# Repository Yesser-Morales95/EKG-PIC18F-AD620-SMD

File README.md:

# EKG-PIC18F-AD620-SMD
C, Labview.

Esquematico Eagle cadsoft .BRD .SCH

Design 

Board

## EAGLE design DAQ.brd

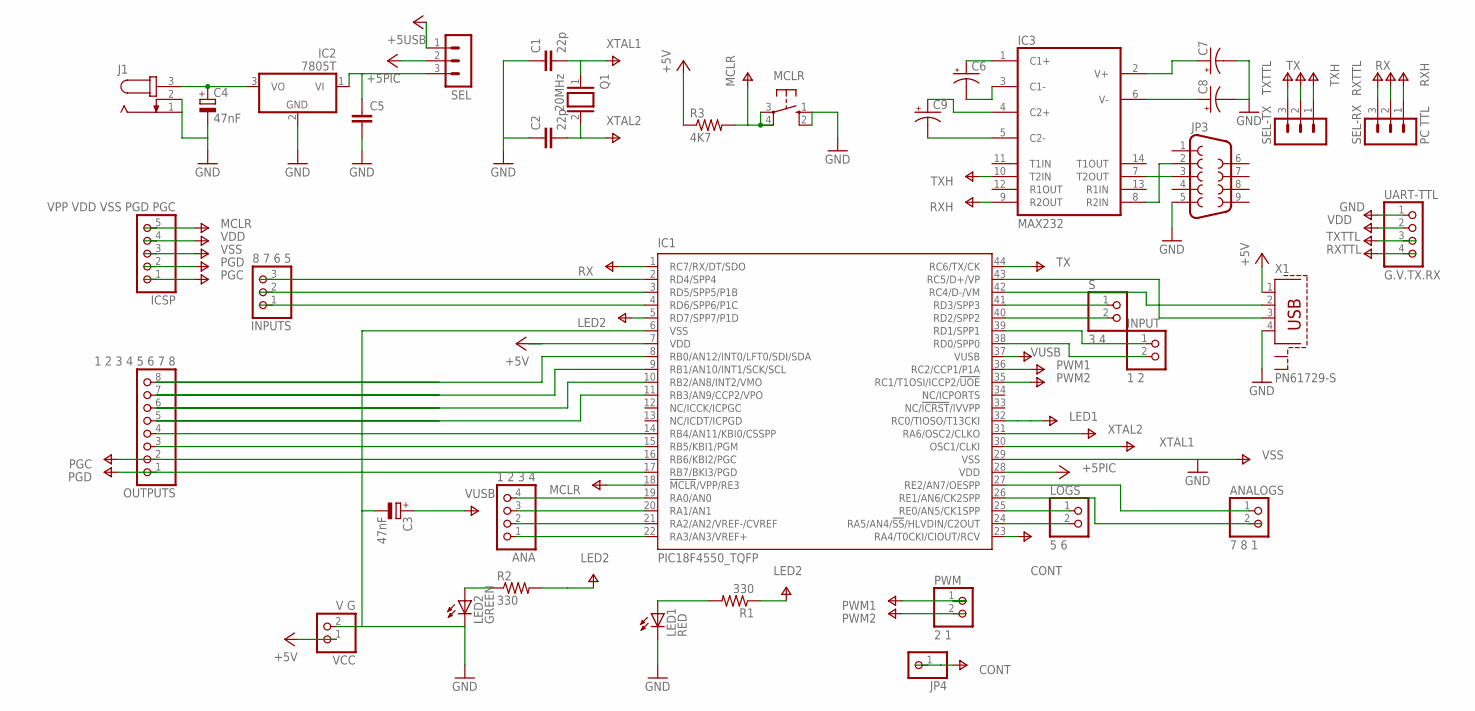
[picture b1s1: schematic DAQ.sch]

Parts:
ANA: 1 2 3 4; 1X04
ANALOGS: 7 8 1; 1X02
C1, C2: 22p; C025-024X044
C3, C4: 47nF; E2,5-6E
C5: C-EU050-035X075; C050-035X075
C6, C7, C8, C9: CPOL-USE2.5-6; E2,5-6
IC1: PIC18F4550_TQFP; TQFP44
IC2: 7805T; TO220H
IC3: MAX232; DIL16
ICSP: VPP VDD VSS PGD PGC; 1X05
INPUT: 1 2; 1X02
INPUTS: 8 7 6 5; 1X03
J1: JACK-PLUG0; SPC4077
JP3: DB9MALE; DB9_MALE
JP4: PINHD-1X1; 1X01
LED1: RED; LED3MM
LED2: GREEN; LED3MM
LOGS: 5 6; 1X02
MCLR: 10-XX; B3F-10XX
OUTPUTS: 1 2 3 4 5 6 7 8; 1X08
PWM: 2 1; 1X02
Q1: 20MHz; QS
R1, R2: 330; 0207/10
R3: 4K7; 0207/10
S: 3 4; 1X02
SEL: MA03-1
SEL-RX: PC TTL; MA03-1
SEL-TX: MA03-1
UART-TTL: G.V.TX.RX; 1X04
VCC: V G; 1X02
X1: PN61729-S

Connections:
+5PIC: IC1.7 (VDD), IC1.28 (VDD), IC3.16 (VCC), ICSP.4, R3.1, SEL.2, UART-TTL.2, VCC.1
+5USB: SEL.1, X1.1
CONT: IC1.23 (RA4/T0CKI/CIOUT/RCV), JP4.1
GND: C1.1, C2.1, C3.-, C4.-, C5.2, C7.-, C8.-, IC1.6 (VSS), IC1.29 (VSS), IC2.2 (GND), IC3.15 (GND), ICSP.3, J1.1, J1.2, JP3.5, LED1.K (C), LED2.K (C), MCLR.1 (S), MCLR.2 (S1), UART-TTL.1, VCC.2, X1.4
LED1: IC1.32 (RC0/TIOSO/T13CKI), R2.2
LED2: IC1.5 (RD7/SPP7/P1D), R1.1
MCLR: IC1.18 (!MCLR!/VPP/RE3), ICSP.5, MCLR.3, MCLR.4 (P1), R3.2
unnamed: IC1.42 (RC4/D-/VM), X1.2
unnamed: C7.+, IC3.2 (V+)
unnamed: C8.+, IC3.6 (V-)
unnamed: IC1.8 (RB0/AN12/INT0/LFT0/SDI/SDA), OUTPUTS.8
unnamed: LED2.A, R2.1
unnamed: C6.+, IC3.1 (C1+)
unnamed: LED1.A, R1.2
unnamed: C6.-, IC3.3 (C1-)
unnamed: IC1.15 (RB5/KBI1/PGM), OUTPUTS.3
unnamed: IC1.14 (RB4/AN11/KBI0/CSSPP), OUTPUTS.4
unnamed: IC1.11 (RB3/AN9/CCP2/VPO), OUTPUTS.5
unnamed: IC1.9 (RB1/AN10/INT1/SCK/SCL), OUTPUTS.7
unnamed: IC1.10 (RB2/AN8/INT2/VMO), OUTPUTS.6
unnamed: C9.+, IC3.4 (C2+)
unnamed: IC1.43 (RC5/D+/VP), X1.3
unnamed: IC1.2 (RD4/SPP4), INPUTS.3
unnamed: IC1.3 (RD5/SPP5/P1B), INPUTS.2
unnamed: IC1.4 (RD6/SPP6/P1C), INPUTS.1
unnamed: IC1.38 (RD0/SPP0), INPUT.2
unnamed: C9.-, IC3.5 (C2-)
unnamed: IC1.40 (RD2/SPP2), S.2
unnamed: IC1.41 (RD3/SPP3), S.1
unnamed: ANA.4, IC1.19 (RA0/AN0)
unnamed: ANA.3, IC1.20 (RA1/AN1)
unnamed: ANA.2, IC1.21 (RA2/AN2/VREF-/CVREF)
unnamed: ANA.1, IC1.22 (RA3/AN3/VREF+)
unnamed: IC1.24 (RA5/AN4/!SS!/HLVDIN/C2OUT), LOGS.2
unnamed: IC1.25 (RE0/AN5/CK1SPP), LOGS.1
unnamed: IC1.39 (RD1/SPP1), INPUT.1
unnamed: ANALOGS.2, IC1.26 (RE1/AN6/CK2SPP)
unnamed: ANALOGS.1, IC1.27 (RE2/AN7/OESPP)
unnamed: IC3.7 (T2OUT), JP3.3
unnamed: IC3.8 (R2IN), JP3.2
unnamed: C4.+, IC2.3 (VO), J1.3
unnamed: C5.1, IC2.1 (VI), SEL.3
PGC: IC1.16 (RB6/KBI2/PGC), ICSP.1, OUTPUTS.2
PGD: IC1.17 (RB7/BKI3/PGD), ICSP.2, OUTPUTS.1
PWM1: IC1.36 (RC2/CCP1/P1A), PWM.1
PWM2: IC1.35 (RC1/T1OSI/ICCP2/!UOE), PWM.2
RX: IC1.1 (RC7/RX/DT/SDO), SEL-RX.2
RXH: IC3.9 (R2OUT), SEL-RX.1
RXTTL: SEL-RX.3, UART-TTL.4
TX: IC1.44 (RC6/TX/CK), SEL-TX.2
TXH: IC3.10 (T2IN), SEL-TX.1
TXTTL: SEL-TX.3, UART-TTL.3
VUSB: C3.+, IC1.37 (VUSB)
XTAL1: C1.2, IC1.30 (OSC1/CLKI), Q1.1
XTAL2: C2.2, IC1.31 (RA6/OSC2/CLKO), Q1.2

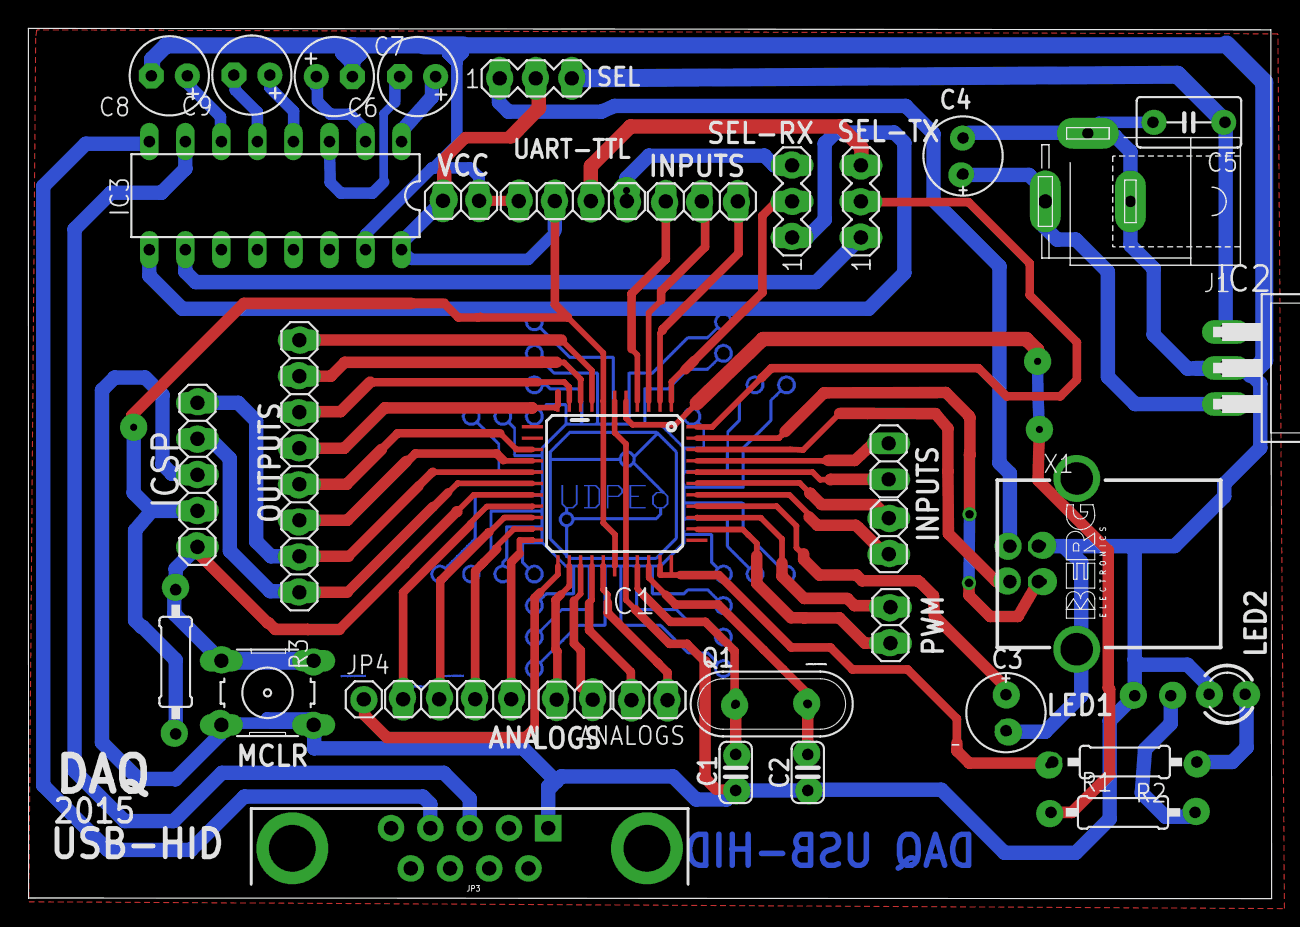
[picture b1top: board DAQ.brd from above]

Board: 2 copper layers, 87.6 x 61.4 mm, 37 parts (1 on the bottom side), 55 nets.

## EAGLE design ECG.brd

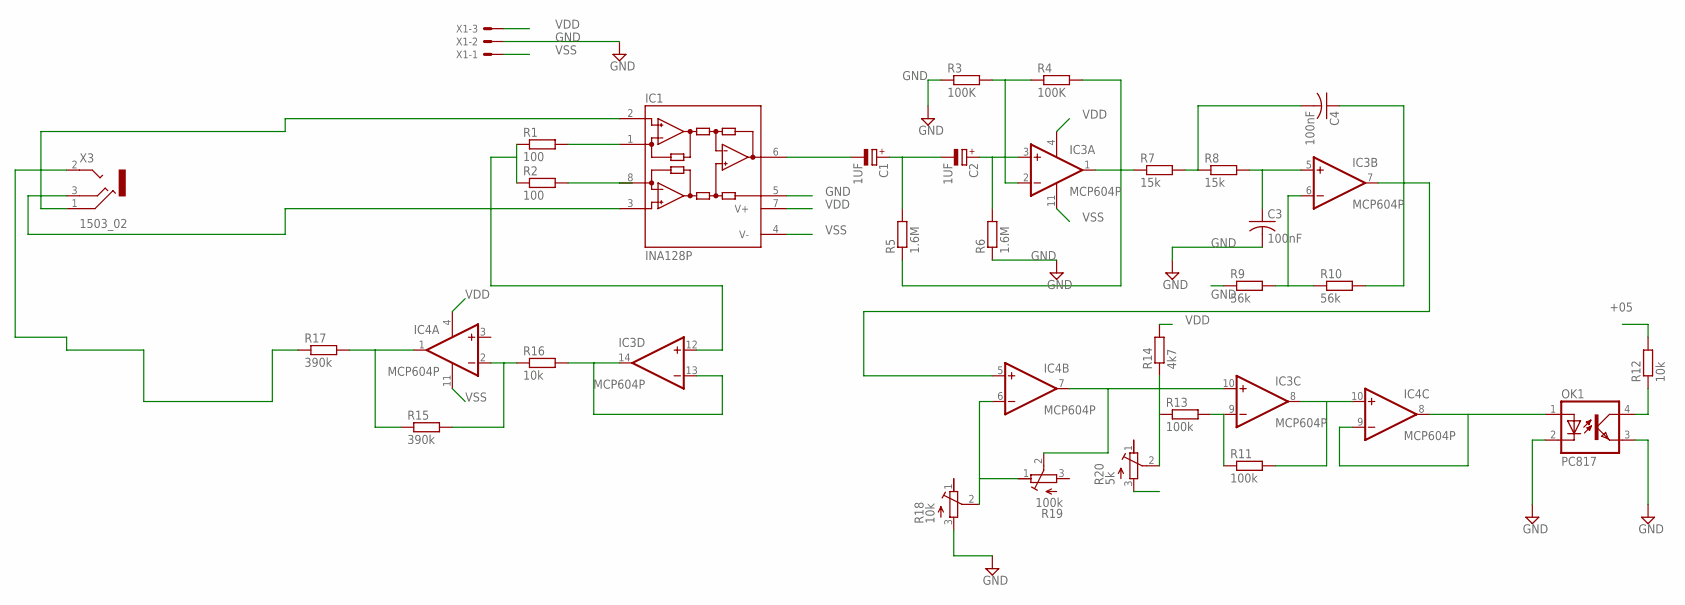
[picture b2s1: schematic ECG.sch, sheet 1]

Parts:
C1, C2: 1UF; E5-6
C3, C4: 100nF; C050-030X075
IC1: INA128P; DIL08
IC3, IC4: MCP604P; DIL14
OK1: PC817; DIL04
R1, R2: 100; 0207/10
R3, R4: 100K; 0207/10
R5, R6: 1.6M; 0207/10
R7, R8: 15k; 0207/10
R9, R10: 56k; 0207/10
R11, R13: 100k; 0207/10
R12, R16: 10k; 0207/10
R14: 4k7; 0207/10
R15, R17: 390k; 0207/10
R18: 10k; RTRIMT18
R19: 100k; RTRIMT18
R20: 5k; RTRIMT18
X1: KK-156-3
X3: 1503_02

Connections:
+05: R12.2; also elsewhere on the board
GND: C3.2, IC1.5 (REF), OK1.2 (C), OK1.3 (EMIT), R3.1, R6.1, R9.1, R18.3 (A), X1.2; also elsewhere on the board
unnamed: IC3.9 (-IN), R11.1, R13.2
unnamed: IC1.1 (RG), R1.2
unnamed: IC1.8 (RG), R2.2
unnamed: IC3.12 (+IN), R1.1, R2.1
unnamed: IC1.2 (-IN), X3.1
unnamed: IC3.13 (-IN), IC3.14 (OUT), R16.2
unnamed: IC4.2 (-IN), R15.2, R16.1
unnamed: IC4.1 (OUT), R15.1, R17.2
unnamed: R17.1, X3.2
unnamed: IC1.3 (+IN), X3.3
unnamed: C1.-, IC1.6 (OUT)
unnamed: C1.+, C2.-, R5.2
unnamed: C2.+, IC3.3 (+IN), R6.2
unnamed: IC3.1 (OUT), R4.2, R5.1, R7.1
unnamed: C4.2, R7.2, R8.1
unnamed: IC3.2 (-IN), R3.2, R4.1
unnamed: C3.1, IC3.5 (+IN), R8.2
unnamed: IC3.6 (-IN), R9.2, R10.1
unnamed: C4.1, IC3.7 (OUT), IC4.5 (+IN), R10.2
unnamed: IC3.10 (+IN), IC4.7 (OUT), R19.2 (S)
unnamed: IC4.6 (-IN), R18.2 (S), R19.1 (E)
unnamed: R13.1, R14.1, R20.2 (S)
unnamed: IC3.8 (OUT), IC4.10 (+IN), R11.2
VDD: IC1.7 (V+), IC3.4 (V+), IC4.4 (V+), R14.2, X1.3; also elsewhere on the board
VECG: IC4.8 (OUT), IC4.9 (-IN), OK1.1 (A); also elsewhere on the board
VECG1: OK1.4 (COL), R12.1; also elsewhere on the board
VSS: IC1.4 (V-), IC3.11 (V-), IC4.11 (V-), R20.3 (A), X1.1

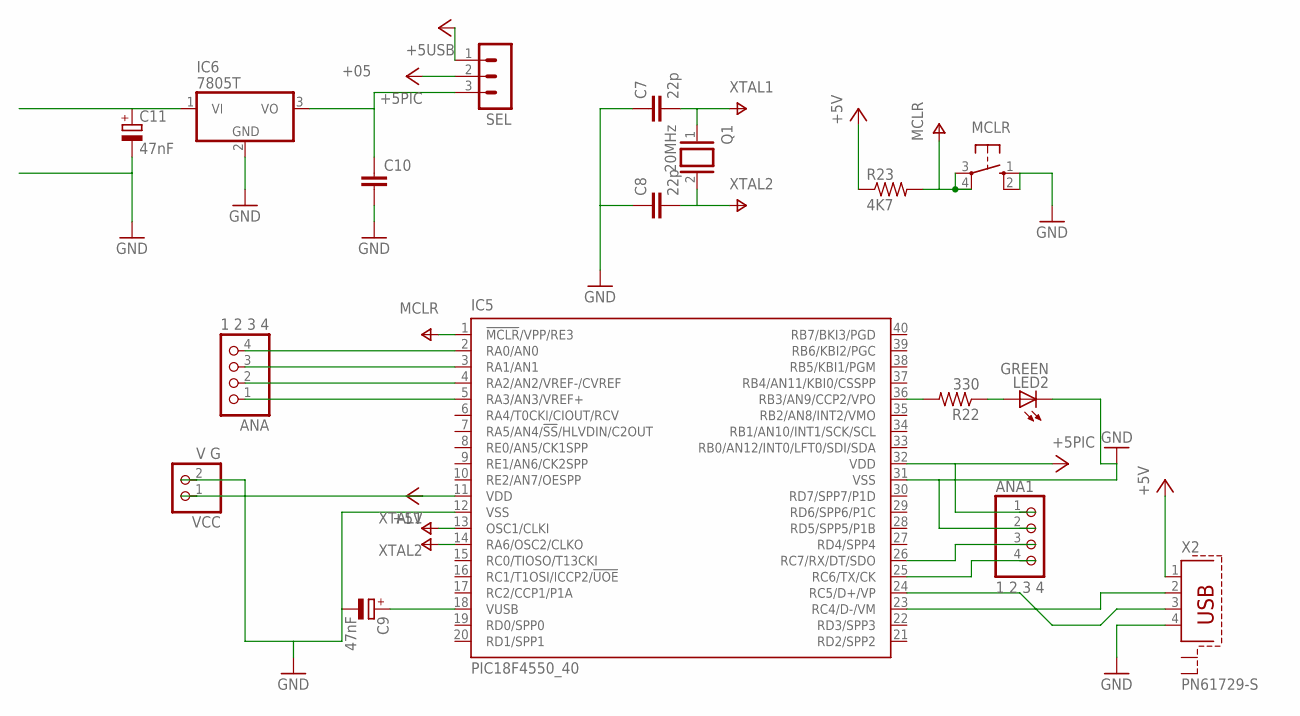
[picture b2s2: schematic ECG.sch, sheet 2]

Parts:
ANA, ANA1: 1 2 3 4; 1X04
C7, C8: 22p; C025-024X044
C9, C11: 47nF; E2,5-6E
C10: C-EU050-035X075; C050-035X075
IC5: PIC18F4550_40; DIL40
IC6: 7805T; TO220H
LED2: GREEN; LED3MM
MCLR: 10-XX; B3F-10XX
Q1: 20MHz; QS
R22: 330; 0207/10
R23: 4K7; 0207/10
SEL: MA03-1
VCC: V G; 1X02
X2: PN61729-S

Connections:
+05: C10.1, IC6.3 (VO), SEL.3; also elsewhere on the board
+5PIC: ANA1.1, IC5.11 (VDD), IC5.32 (VDD), R23.1, SEL.2, VCC.1
+5USB: SEL.1, X2.1
GND: ANA1.2, C7.1, C8.1, C9.-, C10.2, C11.-, IC5.12 (VSS), IC5.31 (VSS), IC6.2 (GND), LED2.K (C), MCLR.1 (S), MCLR.2 (S1), VCC.2, X2.4; also elsewhere on the board
MCLR: IC5.1 (!MCLR!/VPP/RE3), MCLR.3, MCLR.4 (P1), R23.2
unnamed: ANA1.3, IC5.26 (RC7/RX/DT/SDO)
unnamed: ANA1.4, IC5.25 (RC6/TX/CK)
unnamed: IC5.36 (RB3/AN9/CCP2/VPO), R22.2
unnamed: LED2.A, R22.1
unnamed: IC5.23 (RC4/D-/VM), X2.2
unnamed: IC5.24 (RC5/D+/VP), X2.3
unnamed: C9.+, IC5.18 (VUSB)
unnamed: ANA.2, IC5.4 (RA2/AN2/VREF-/CVREF)
unnamed: ANA.1, IC5.5 (RA3/AN3/VREF+)
VDD: C11.+, IC6.1 (VI); also elsewhere on the board
VECG: ANA.4, IC5.2 (RA0/AN0); also elsewhere on the board
VECG1: ANA.3, IC5.3 (RA1/AN1); also elsewhere on the board
XTAL1: C7.2, IC5.13 (OSC1/CLKI), Q1.1
XTAL2: C8.2, IC5.14 (RA6/OSC2/CLKO), Q1.2

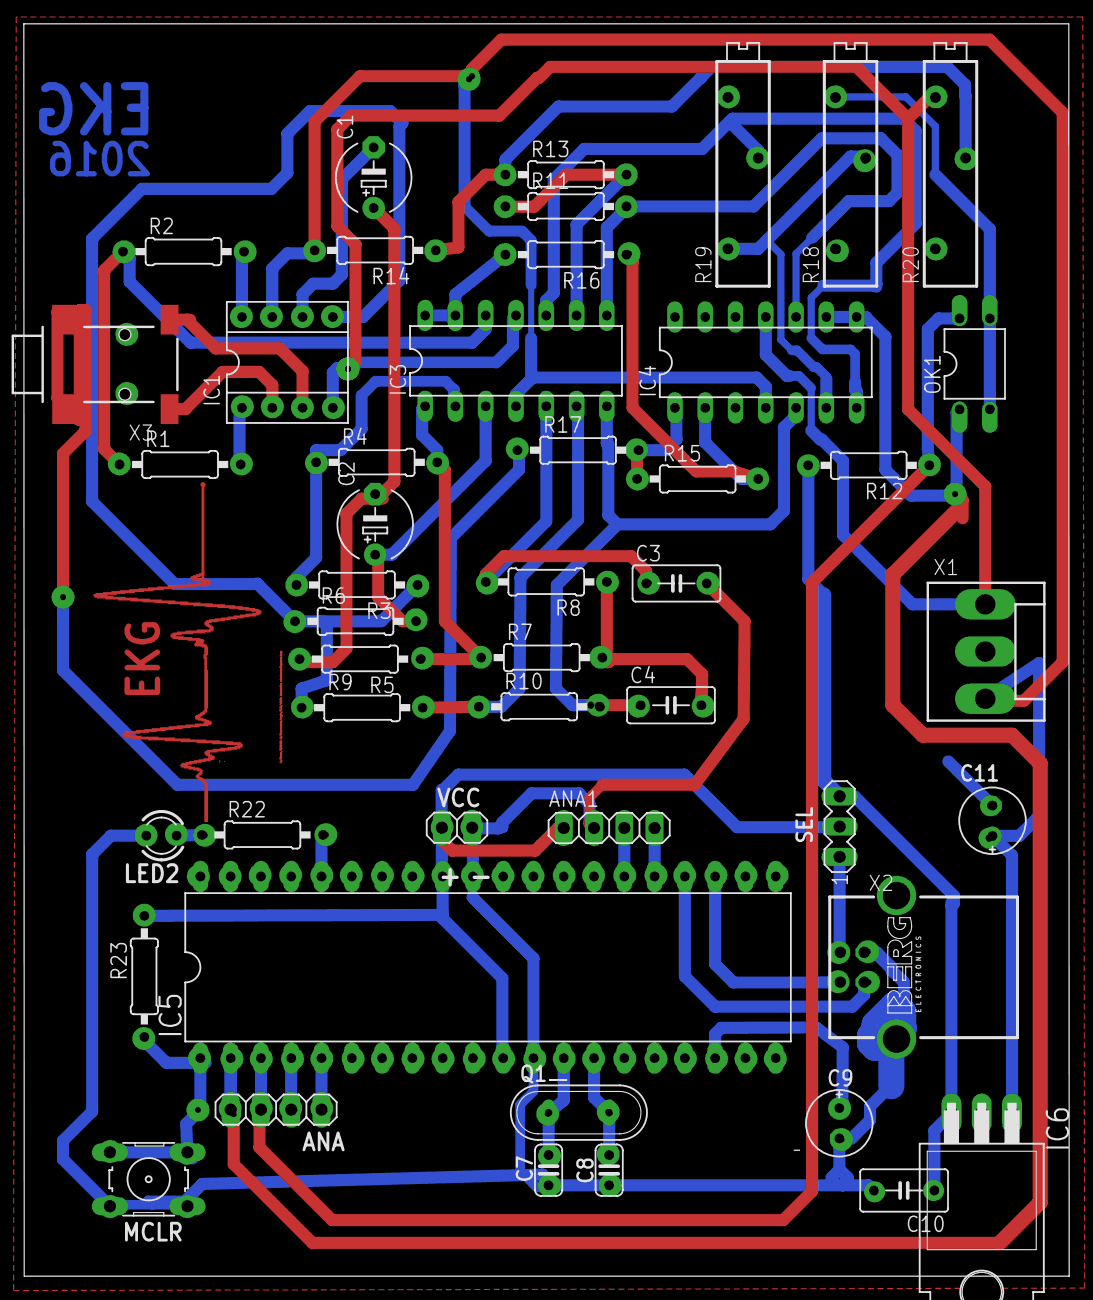
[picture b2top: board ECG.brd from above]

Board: 2 copper layers, 87.7 x 105.1 mm, 47 parts (0 on the bottom side), 43 nets.

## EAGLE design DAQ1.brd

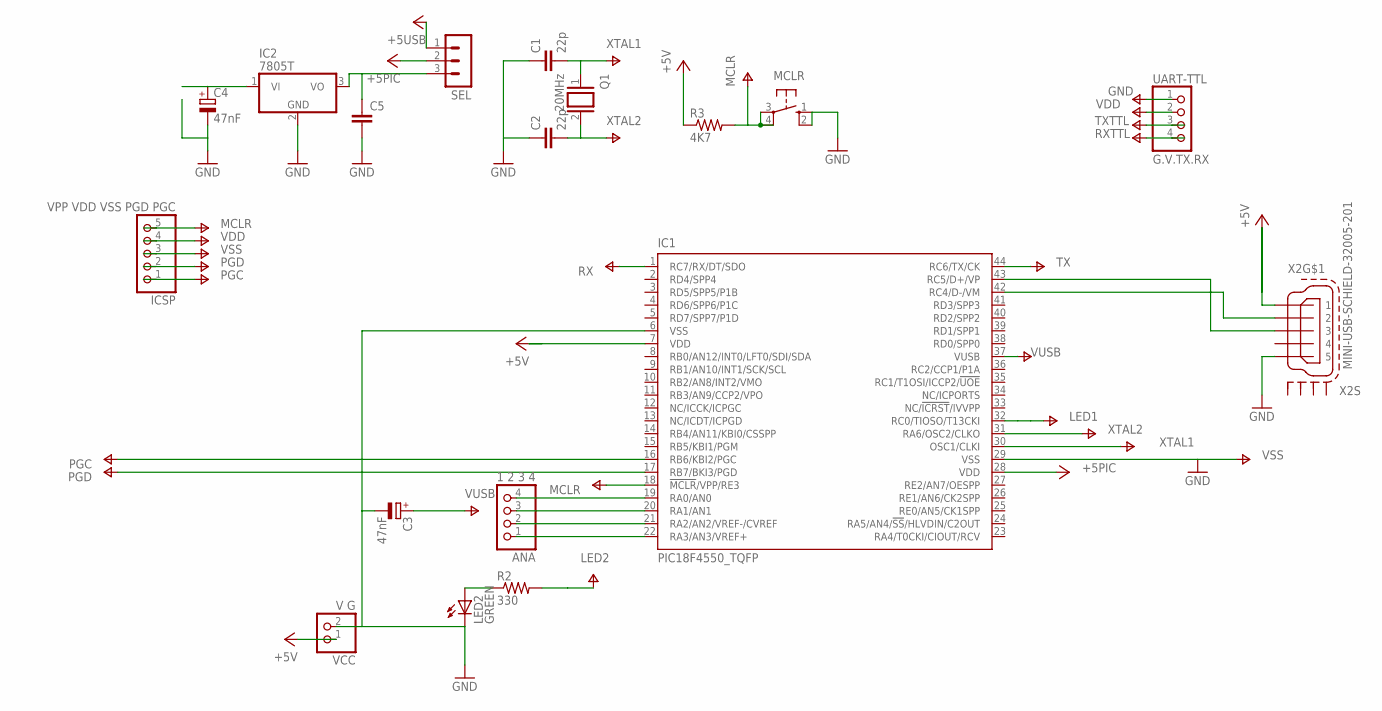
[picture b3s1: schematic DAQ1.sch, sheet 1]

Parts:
ANA: 1 2 3 4; 1X04
C1, C2: 22p; C025-024X044
C3, C4: 47nF; E2,5-6E
C5: C-EU050-035X075; C050-035X075
IC1: PIC18F4550_TQFP; TQFP44
IC2: 7805T; TO220H
ICSP: VPP VDD VSS PGD PGC; 1X05
LED2: GREEN; LED3MM
MCLR: 10-XX; B3F-10XX
Q1: 20MHz; QS
R2: 330; 0207/10
R3: 4K7; 0207/10
SEL: MA03-1
UART-TTL: G.V.TX.RX; 1X04
VCC: V G; 1X02
X2: MINI-USB-SCHIELD-32005-201; 32005-201

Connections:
+5PIC: IC1.7 (VDD), IC1.28 (VDD), ICSP.4, R3.1, SEL.2, UART-TTL.2, VCC.1
+5USB: SEL.1, X2.1
AN0: ANA.4, IC1.19 (RA0/AN0); also elsewhere on the board
GND: C1.1, C2.1, C3.-, C4.-, C5.2, IC1.6 (VSS), IC1.29 (VSS), IC2.2 (GND), ICSP.3, LED2.K (C), MCLR.1 (S), MCLR.2 (S1), UART-TTL.1, VCC.2, X2.5; also elsewhere on the board
LED1: IC1.32 (RC0/TIOSO/T13CKI), R2.2
MCLR: IC1.18 (!MCLR!/VPP/RE3), ICSP.5, MCLR.3, MCLR.4 (P1), R3.2
unnamed: IC1.42 (RC4/D-/VM), X2.2
unnamed: LED2.A, R2.1
unnamed: IC1.43 (RC5/D+/VP), X2.3
unnamed: ANA.3, IC1.20 (RA1/AN1)
unnamed: ANA.2, IC1.21 (RA2/AN2/VREF-/CVREF)
unnamed: ANA.1, IC1.22 (RA3/AN3/VREF+)
unnamed: C5.1, IC2.3 (VO), SEL.3
PGC: IC1.16 (RB6/KBI2/PGC), ICSP.1
PGD: IC1.17 (RB7/BKI3/PGD), ICSP.2
RX: IC1.1 (RC7/RX/DT/SDO), UART-TTL.4
TX: IC1.44 (RC6/TX/CK), UART-TTL.3
VDD: C4.+, IC2.1 (VI); also elsewhere on the board
VUSB: C3.+, IC1.37 (VUSB)
XTAL1: C1.2, IC1.30 (OSC1/CLKI), Q1.1
XTAL2: C2.2, IC1.31 (RA6/OSC2/CLKO), Q1.2

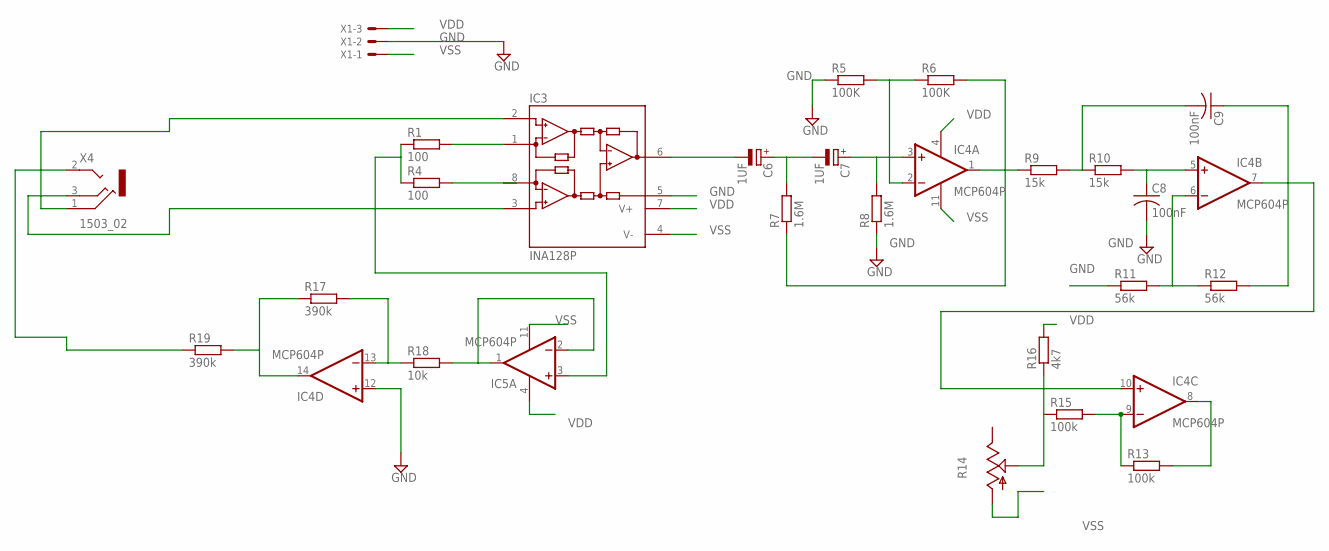
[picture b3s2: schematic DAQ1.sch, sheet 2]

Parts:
C6, C7: 1UF; E5-6
C8, C9: 100nF; C050-030X075
IC3: INA128P; DIL08
IC4, IC5: MCP604P; DIL14
R1, R4: 100; 0207/10
R5, R6: 100K; 0207/10
R7, R8: 1.6M; 0207/10
R9, R10: 15k; 0207/10
R11, R12: 56k; 0207/10
R13, R15: 100k; 0207/10
R14: TRIM_US-CA6V; CA6V
R16: 4k7; 0207/10
R17, R19: 390k; 0207/10
R18: 10k; 0207/10
X1: KK-156-3
X4: 1503_02

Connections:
AN0: IC4.8 (OUT), R13.2; also elsewhere on the board
GND: C8.2, IC3.5 (REF), IC4.12 (+IN), R5.1, R8.1, R11.1, X1.2; also elsewhere on the board
unnamed: IC5.3 (+IN), R1.1, R4.1
unnamed: IC4.1 (OUT), R6.2, R7.1, R9.1
unnamed: IC3.8 (RG), R4.2
unnamed: IC4.9 (-IN), R13.1, R15.2
unnamed: IC5.1 (OUT), IC5.2 (-IN), R18.2
unnamed: IC4.13 (-IN), R17.2, R18.1
unnamed: IC4.14 (OUT), R17.1, R19.2
unnamed: R19.1, X4.2
unnamed: R14.S, R15.1, R16.1
unnamed: C6.-, IC3.6 (OUT)
unnamed: C6.+, C7.-, R7.2
unnamed: C7.+, IC4.3 (+IN), R8.2
unnamed: C9.2, R9.2, R10.1
unnamed: IC4.2 (-IN), R5.2, R6.1
unnamed: C8.1, IC4.5 (+IN), R10.2
unnamed: IC4.6 (-IN), R11.2, R12.1
unnamed: C9.1, IC4.7 (OUT), IC4.10 (+IN), R12.2
unnamed: IC3.2 (-IN), X4.1
unnamed: IC3.3 (+IN), X4.3
unnamed: IC3.1 (RG), R1.2
VDD: IC3.7 (V+), IC4.4 (V+), IC5.4 (V+), R16.2, X1.3; also elsewhere on the board
VSS: IC3.4 (V-), IC4.11 (V-), IC5.11 (V-), R14.A, X1.1

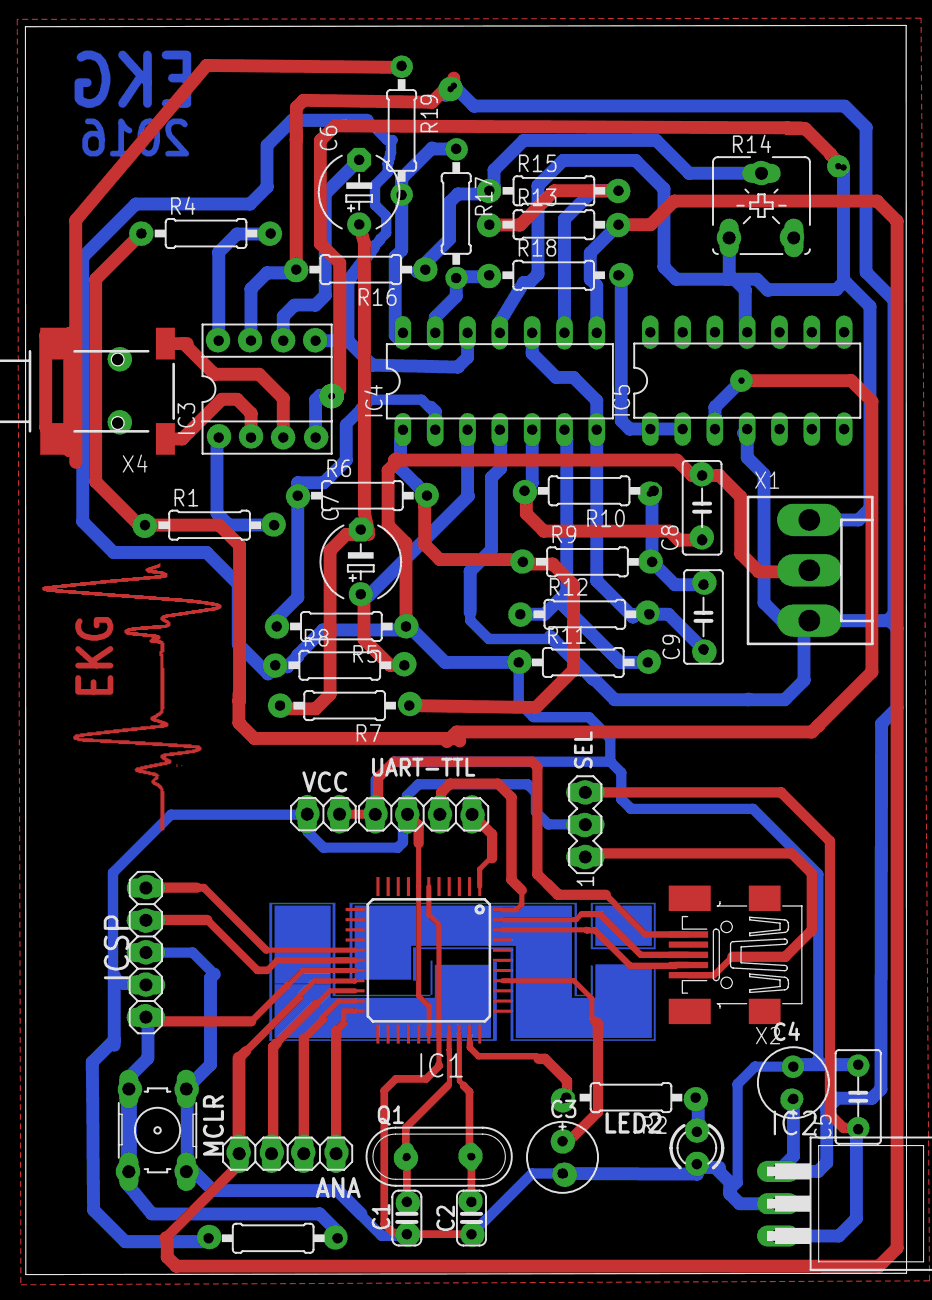
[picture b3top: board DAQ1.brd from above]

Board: 2 copper layers, 69.3 x 98.2 mm, 44 parts (0 on the bottom side), 42 nets.

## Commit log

2017-03-03 :boom::camel: Added .gitattributes & .gitignore files
2017-03-03 C
    Program two versions
2017-06-02 Add files via upload
    Diseño de PCB EAGLE cadsoft
2017-06-02 Create README.md
    ECG description

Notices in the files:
parts and their libraries:
SparkFun-Connectors: Licensing: Creative Commons ShareAlike 4.0 International - https://creativecommons.org/licenses/by-sa/4.0
